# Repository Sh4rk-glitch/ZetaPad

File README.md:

# ZetaPad

Small CircuitPython firmware for a 4-key macropad (W, A, S, D) and a rotary encoder for system volume control. Designed for Seeed XIAO RP2040 but pins can be changed.

Files
- `main.py` — firmware to copy onto the `CIRCUITPY` drive.
- `requirements.txt` — libraries needed from the CircuitPython Bundle.

Wiring (suggested pins)
- Buttons (4): `GP0`, `GP1`, `GP2`, `GP3` — connect one side of each button to the pin, the other side to GND.
- Rotary encoder A: `GP4`  
- Rotary encoder B: `GP5`  
- Encoder push switch: `GP6` — optional; press toggles mute.

Notes about wiring
- Buttons use internal pull-ups; wire them to GND when pressed (active low).
- If your encoder has integrated pull-ups or requires different wiring, adapt pins and code accordingly.

Installing CircuitPython and libraries
1. Install CircuitPython for the XIAO RP2040: download the correct UF2 from circuitpython.org and flash it to the board. The board will mount as `CIRCUITPY`.
2. Copy `main.py` to the root of `CIRCUITPY`.
3. Create a `lib` folder on `CIRCUITPY` and add the required library modules. See `requirements.txt` for the libraries to include from the CircuitPython bundle.

Required libraries
See `requirements.txt`. At minimum, include:
- `adafruit_hid`  
- `adafruit_debouncer`  

Changing key behavior
- The default keys are `W, A, S, D` (good for gaming). To use arrow keys instead, edit `KEY_MAP` in `main.py` and replace the entries with `Keycode.UP`, `Keycode.LEFT`, `Keycode.DOWN`, `Keycode.RIGHT`.

Customization
- Change `BUTTON_PINS`, `ENCODER_A`, `ENCODER_B`, and `ENCODER_SW` at the top of `main.py` to match your physical wiring.

Usage
- Plug the XIAO into your PC. `main.py` will run and present as a USB keyboard + consumer control device. Press buttons to send/hold WASD; rotate encoder to change system volume; press encoder button to mute.

Troubleshooting
- If you don't see HID behavior, ensure CircuitPython is installed and you copied required libraries into `lib`.
- Use the serial REPL (Mu or screen/serial tool) to see printouts for debugging.

License
- Use/modify freely for personal projects.

# Images

Overall Hackpad:

Full Schematic:

Full PCB:

Bill of Materials:
- 8 Key caps, 4 WASD and 4 ARROW KEY ones (interchangable)
- One XIAO RP2040 
- TWO rotary encoders, incase one gets messed up or one more for future improvements
- One LCD Screen (also for future improvements such as a status update showing users cpu usage, gpu usage, etc)
- 12 CHERRY MX-Style switches 
- SK6812 MINI-E LEDs (4, for future improvements, one for charging, one for charged, one for num lock, one for caps)
- M3x16mm screws (x16)
- M3x5mx4mm heatset inserts (x16)
- One 3D Printer
- One Saughtering Machine

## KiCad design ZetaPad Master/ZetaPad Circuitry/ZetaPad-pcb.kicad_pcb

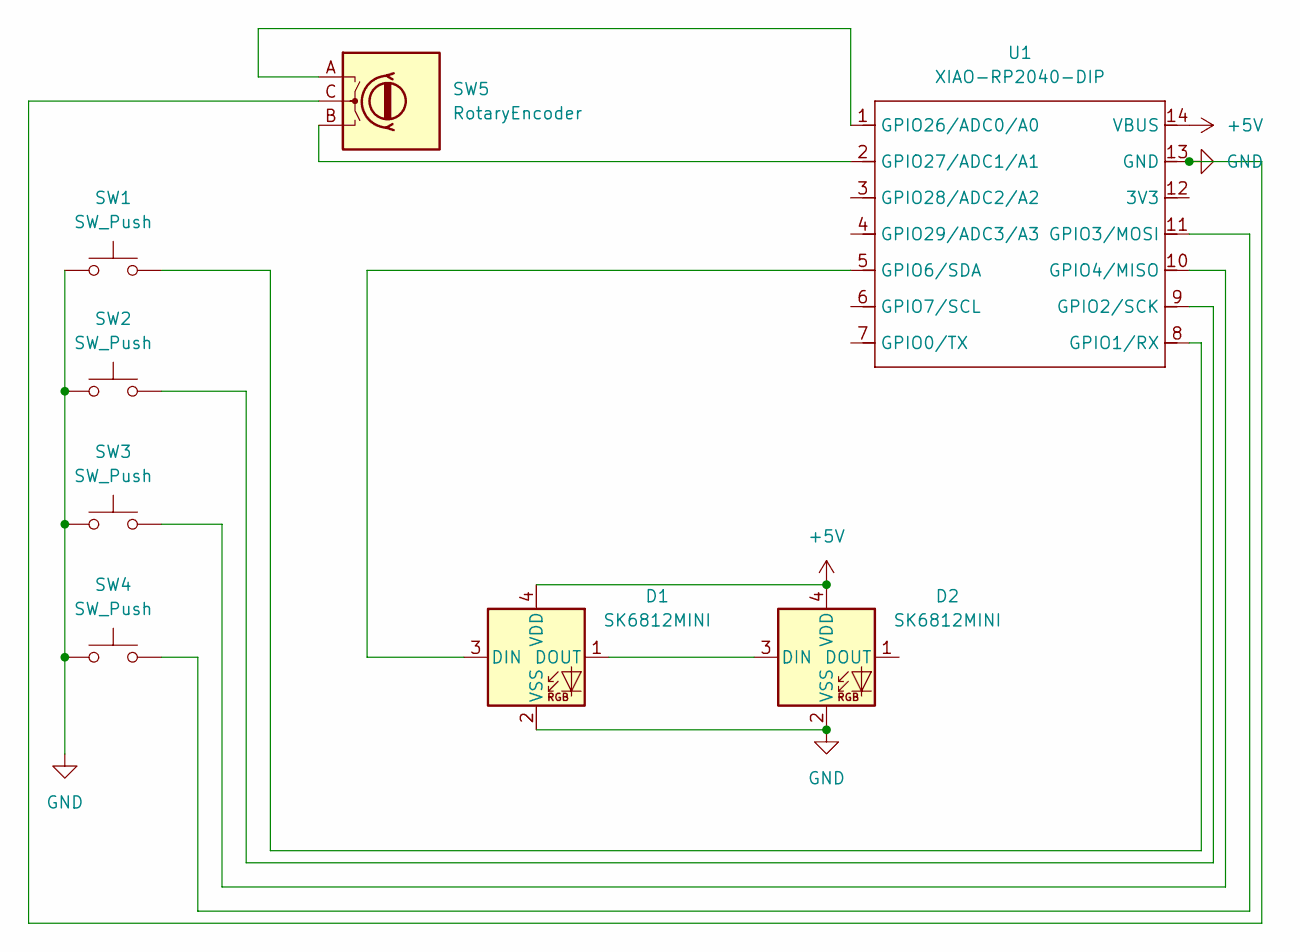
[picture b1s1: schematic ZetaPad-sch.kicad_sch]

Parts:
D1, D2: SK6812MINI; LED_SK6812MINI_PLCC4_3.5x3.5mm_P1.75mm
SW1, SW2, SW3, SW4: SW_Push; SW_Cherry_MX_1.00u_PCB
SW5: RotaryEncoder; RotaryEncoder_Alps_EC11E_Vertical_H20mm
U1: XIAO-RP2040-DIP

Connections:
+5V: D1.4 (VDD), D2.4 (VDD), U1.14 (VBUS)
GND: D1.2 (VSS), D2.2 (VSS), SW1.1, SW2.1, SW3.1, SW4.1, SW5.C, U1.13 (GND)
unnamed: D1.3 (DIN), U1.5 (GPIO6/SDA)
unnamed: D1.1 (DOUT), D2.3 (DIN)
unnamed: SW1.2, U1.8 (GPIO1/RX)
unnamed: SW2.2, U1.9 (GPIO2/SCK)
unnamed: SW4.2, U1.11 (GPIO3/MOSI)
unnamed: SW3.2, U1.10 (GPIO4/MISO)
unnamed: SW5.A, U1.1 (GPIO26/ADC0/A0)
unnamed: SW5.B, U1.2 (GPIO27/ADC1/A1)

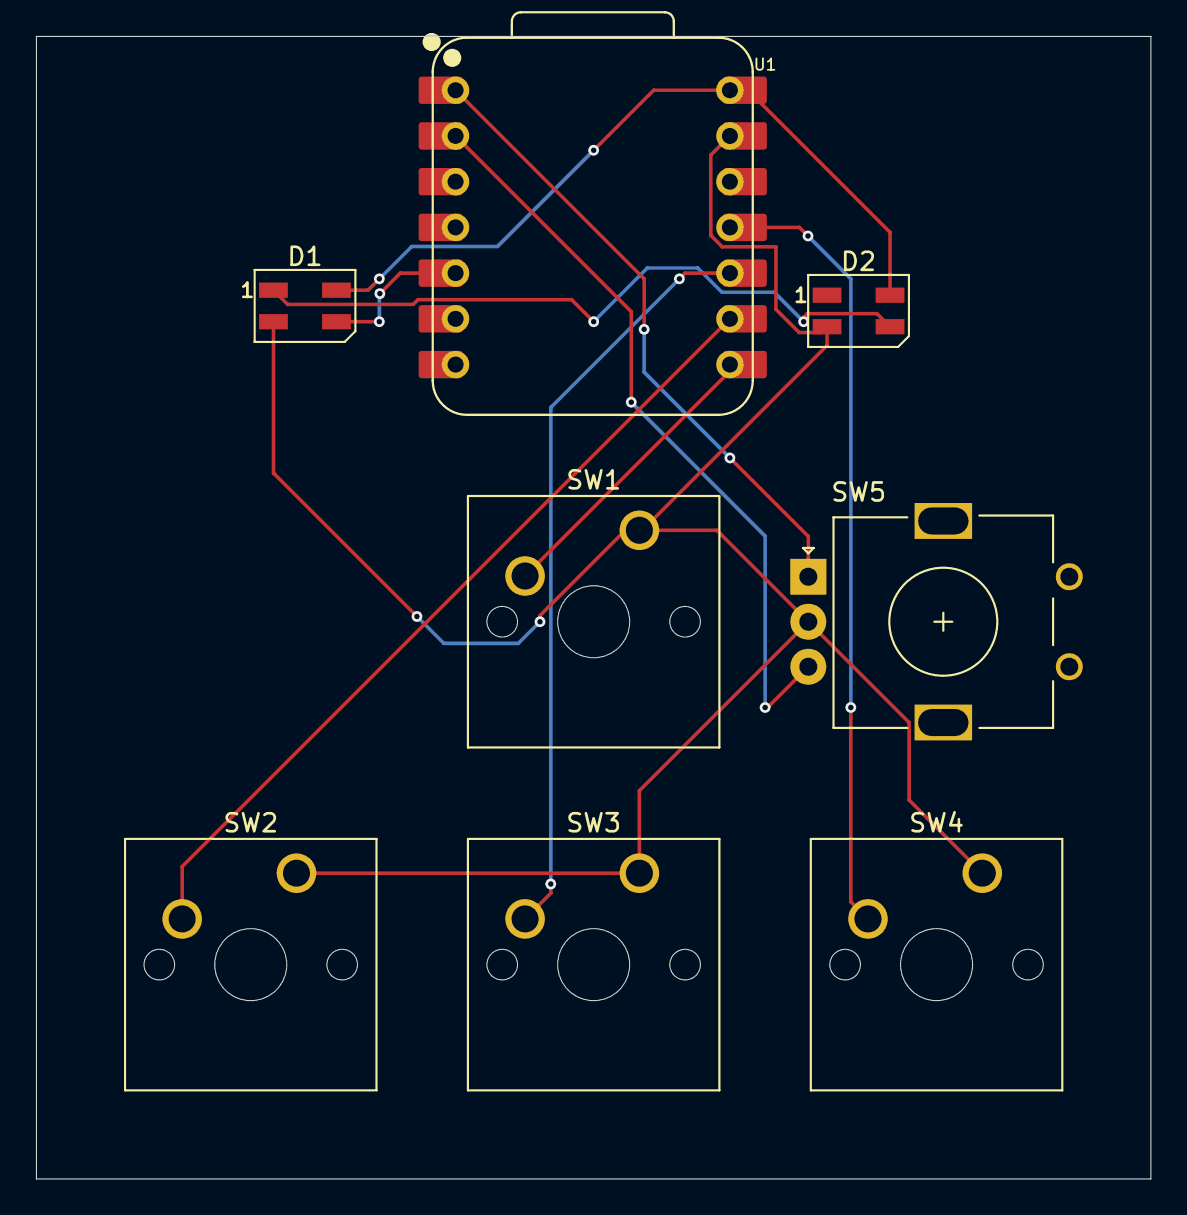
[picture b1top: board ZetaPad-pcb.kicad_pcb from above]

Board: 2 copper layers, 61.9 x 63.5 mm, 8 parts (0 on the bottom side), 10 nets.

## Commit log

2025-12-04 CAD + Wiring files
2025-12-04 Code
2025-12-04 Update README with XIAO RP2040 Macropad details
    Added detailed information about the XIAO RP2040 Macropad, including wiring, installation, and usage instructions.
2025-12-04 Adding stp files
2025-12-04 Code+CAD+Circuitry
2025-12-04 Add images section to README
    Added images section with overall Hackpad image.
2025-12-04 Update README with images and BOM
    Added images and bill of materials to README.
2025-12-04 Add PCB image to README
2025-12-04 Fix duplicate entries in Bill of Materials
    Removed duplicate entries from the Bill of Materials section.
2025-12-04 Fix formatting of Bill of Materials in README
2025-12-06 Fix header formatting for Images section in README
2025-12-06 Rename project to ZetaPad
    Updated project name and description in README.
